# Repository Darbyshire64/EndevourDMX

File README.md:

# EndevourDMX
This is a custom DMX Tranciver Platform Designed for both reciving and controling DMX. Using an ESP32-C3 With Onboard WIFI

>[!Warning]
> Use This PCB at your own Risk. I cannot take liability if it breake's and or causes damage to equipment. This has not been tested and there is no garrentee of upholding to any level of quality/functionality.

https://github.com/user-attachments/assets/77d9e712-4af0-4d90-8f60-33b776832eaa

## Curently Availible Firmware Modes
  - Cable Tester
  - Light Controler

## Goals
  - Control One DMX Universe
  - Recive DMX and make signal qaulity Reports.
  - WIFI Based Control.
  - Display Status and Other INFO With Inbuilt OLED

## How It Works

It allows for DMX Passthrough so if something where to hapen to the MCU the DMX signal Could still passthrough pasiveley without power. The A,B Data lines are protected by a TVS Diode and 100 ohm resistors this cleans up any interfearence in the transmision. this is then sent the the MAX845E Chip to convert the data into easy to recive serieal data for the ESP. As the DMX lighting protocol uses RS845 Serieal the MAX845E is neccesary to control TX/RX the signal.

# Photos
## PCB

## Case

# BOM

I know this BOM is Expensive But its cheaper than the equivlent device i was trying to redesign but better, Called MyDMX 3.0 witch is 401.74 USD

<a href="https://www.djkit.com/products/american-dj-mydmx-30?variant=51192390254925&country=GB&currency=GBP&utm_medium=product_sync&utm_source=google&utm_content=sag_organic&utm_campaign=sag_organic"> LINK </a>

| QTY | Item                    | Price   | Link        |
|-----|-------------------------|---------|-------------|
|     | PCB Total               | $14.59  |             |
|     | Component Total         | $38.81 |             |
|     | Case Total              | $4.50   |             |
|     | Misc Total              | $13.36   |             |
|     | Total                   | $71.27   |             |

## PCB 

| QTY | Item                    | Price   | Link        |
|-----|-------------------------|---------|-------------|
|  5  | Custom Blue LF HASL PCB | $9.40  |             |
|     | Shipping (GSDL)         | $5.19   |             |
|     | Total                   | $14.59  |             |

## Components

I have chosen Digikey because it has all of my components vs LCSC who has a few of my components in stock as of making the BOM. it would be more cost effective  to buy all the components in one go rather than by two lots of shipping and handeling fees. and A OLEDs components are cheaper via Ali Express.

### Digikey
| QTY | Item                    | Price  | Link        |
|-----|-------------------------|---------|-------------|
|  2  | 1.5KE15CA        | $0.34 | <a href="https://www.digikey.co.uk/en/products/detail/stmicroelectronics/1-5KE15CA/1037261">LINK</a> |
|  1  | 1N4007           | $0.10 | <a href="https://www.digikey.co.uk/en/products/detail/diotec-semiconductor/1N4007/18833652">LINK</a> |
|  1  | MFR-25FBF52-1K8  | $0.10 | <a href="https://www.digikey.co.uk/en/products/detail/yageo/MFR-25FBF52-1K8/9138063">LINK</a> |
|  1  | CFR-12JB-52-3K3  | $0.10 | <a href="https://www.digikey.co.uk/en/products/detail/yageo/CFR-12JB-52-3K3/3989">LINK</a> |
|  2  | MFR-25FBF52-100R | $0.10 | <a href="https://www.digikey.co.uk/en/products/detail/yageo/MFR-25FBF52-100R/12795">LINK</a> |
|  1  | MFR-25FBF52-120R | $0.10 | <a href="https://www.digikey.co.uk/en/products/detail/yageo/MFR-25FTE52-120R/9139747">LINK</a> |
|  1  | 2N3904           | $0.14 | <a href="https://www.digikey.co.uk/en/products/detail/diotec-semiconductor/2N3904/13164701">LINK</a> |
|  3  | WS281B           | $0.68 | <a href="https://www.digikey.co.uk/en/products/detail/sparkfun-electronics/16347/11630204">LINK</a> |
|  1  | MAX485ECSA+      | $5.88 | <a href="https://www.digikey.co.uk/en/products/detail/analog-devices-inc-maxim-integrated/MAX485ECSA/1495336">LINK</a> |
|  1  | IO-XLR3-F-EH     | $2.63 | <a href="https://www.digikey.co.uk/en/products/detail/io-audio-technologies/IO-XLR3-F-EH/9931888">LINK</a> |
|  1  | IO-XLR3-M-EH     | $2.55 | <a href="https://www.digikey.co.uk/en/products/detail/io-audio-technologies/IO-XLR3-M-EH/9931887">LINK</a> |
|  1  | XIAO ESP-32-C3   | $4.99 | <a href="https://www.digikey.co.uk/en/products/detail/seeed-technology-co-ltd/113991054/16652880">LINK</a> |
|  1  | 2.4Ghz Atenna    | $2.20 | <a href="https://www.digikey.co.uk/en/products/detail/seeed-technology-co-ltd/103990623/18724506">LINK</a> |
|  1  | Headers          | $0.24 | <a href="https://www.digikey.co.uk/en/products/detail/seeed-technology-co-ltd/102010490/19176770">LINK</a> |
|     | Shiping          | $6.88 | |
|     | Total Excl Shiping| $21.95 | |
|     | Total Incl Shiping| $29.84 | |

### AliExpress

| QTY | Item                    | Price  | Link        |
|-----|-------------------------|---------|-------------|
|  1  | OLED DISPLAY        | $5.35 | <a href="https://www.aliexpress.com/item/1005008988479159.html?spm=a2g0o.detail.0.0.3f8dP1SHP1SHRr&mp=1&pdp_npi=5%40dis%21USD%21USD%205.35%21USD%202.62%21%21USD%202.62%21%21%21%40211b628117536181461324433e3141%2112000047475624684%21ct%21UK%21-1%21%211%210">LINK</a> |
| | Total Excl Shiping | $5.35 |
| | Toatl Incl Shiping | $8.34 |

## Case

Printed With Printing Legion. Estmiated Shiping Cost Based on prevoious printing legion experiance.

| QTY | Item                    | Price   | Link        |
|-----|-------------------------|---------|-------------|
|  1  | Case                    | $4.50   |             |

## Tool's & Misc

| QTY | Item                    | Price   | Link        |
|-----|-------------------------|---------|-------------|
|  1  | 10g Flux                | $3.32   | <a href="https://www.aliexpress.com/item/1005008562727265.html?spm=a2g0o.detail.0.0.1891tDgOtDgOiD&mp=1&pdp_npi=5%40dis%21USD%21USD%203.32%21USD%200.99%21%21USD%200.99%21%21%21%40211b628117536181317473986e3141%2112000045736601174%21ct%21UK%21-1%21%211%210"> LINK </a> |
|  1  | 50g Solder              | $10.89  | <a href="https://www.aliexpress.com/item/1005007330449968.html?spm=a2g0o.detail.0.0.d802qv9rqv9rOF&mp=1&pdp_npi=5%40dis%21USD%21USD%2010.89%21USD%205.44%21%21USD%205.44%21%21%21%40211b628117536180518621644e3141%2112000040294388218%21ct%21UK%21-1%21%211%210"> LINK </a> |
|  1  | M3 Heatset Inserts      | $2.03   | <a href="https://www.aliexpress.com/item/1005003582355741.html?spm=a2g0o.detail.0.0.330ciNNZiNNZhx&mp=1&pdp_npi=5%40dis%21USD%21USD%202.03%21USD%202.03%21%21USD%202.03%21%21%21%40211b628117536180843722706e3141%2112000026370649756%21ct%21UK%21-1%21%211%210"> LINK </a>  |
|  1  | M3x14mm Screws          | $2.94   | <a href="https://www.aliexpress.com/item/32867841097.html?spm=a2g0o.cart.0.0.5a5b38dafIVPIo&mp=1&pdp_npi=5%40dis%21USD%21USD%202.94%21USD%202.65%21%21USD%202.65%21%21%21%402103892f17536178038338142eac37%2165441947149%21ct%21UK%21-1%21%211%210"> LINK </a> |
| | Total No Discount & Shiping | $19.81 |
| | Total Incl Discounts & Shiping | $13.36|

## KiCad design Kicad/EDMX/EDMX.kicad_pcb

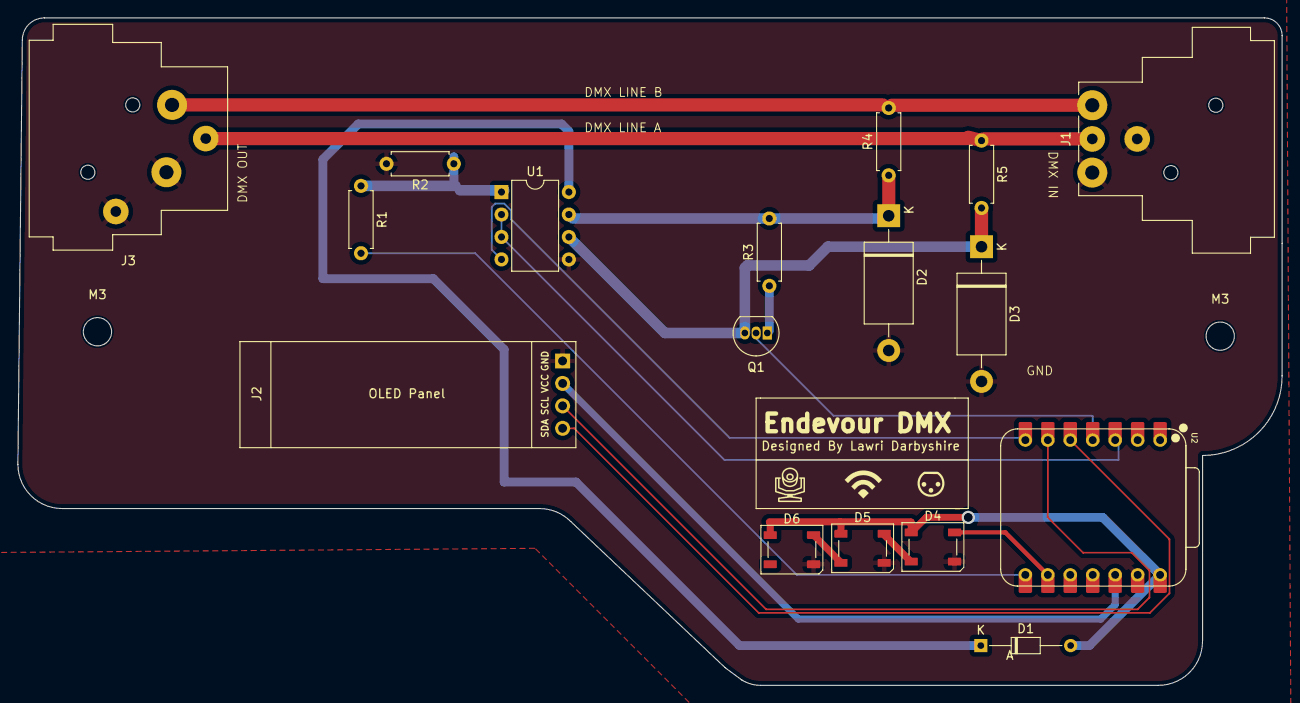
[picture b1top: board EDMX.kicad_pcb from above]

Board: 2 copper layers, 143.0 x 75.5 mm, 19 parts (0 on the bottom side), 18 nets.

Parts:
D1: D; D_DO-34_SOD68_P10.16mm_Horizontal
D2, D3: 1.5KExxCA; D_DO-201AE_P15.24mm_Horizontal
D4: DMX Status; LED_WS2812B_PLCC4_5.0x5.0mm_P3.2mm
D5: WiFi Status; LED_WS2812B_PLCC4_5.0x5.0mm_P3.2mm
D6: Light Control; LED_WS2812B_PLCC4_5.0x5.0mm_P3.2mm
J1: XLR3 IN; Jack_XLR_Neutrik_NC3MAAH_Horizontal
J2: Conn_01x04; SSD1306-0.91-OLED-4pin-128x32
J3: XLR3 OUT; Jack_XLR_Neutrik_NC3FAH2_Horizontal
M3, M3#2: MountingHole_3.2mm_M3
Q1: 2N3904; TO-92_Inline
R1: 3.3kΩ; R_Axial_DIN0207_L6.3mm_D2.5mm_P7.62mm_Horizontal
R2: 1.8kΩ; R_Axial_DIN0207_L6.3mm_D2.5mm_P7.62mm_Horizontal
R3: 120Ω; R_Axial_DIN0207_L6.3mm_D2.5mm_P7.62mm_Horizontal
R4, R5: 100Ω; R_Axial_DIN0207_L6.3mm_D2.5mm_P7.62mm_Horizontal
U1: MAX485E; DIP-8_W7.62mm
U2: XIAO-ESP32-C3-DIP; XIAO-ESP32C3-DIP

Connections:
/5V: R1.1, R2.1, U1.1 (RO)
GND: D2.2 (A2), D3.2 (A2), D4.3 (VSS), D5.3 (VSS), D6.3 (VSS), J1.1, J1.G, J2.1, J3.1, J3.G, R2.2, U1.5 (GND), U2.13 (GND)
unnamed: D2.1 (A1), R3.2, R4.2
unnamed: D3.1 (A1), Q1.3 (C), R5.2, U1.6 (A)
unnamed: D4.2 (DOUT), D5.4 (DIN)
unnamed: D5.2 (DOUT), D6.4 (DIN)
unnamed: J1.2, J3.2, R4.1
unnamed: J1.3, J3.3, R5.1
unnamed: Q1.1 (E), R3.1
RX: R1.2, U2.8 (GPIO20/D7/RX)
SCL: J2.3, U2.6 (GPIO7/D5/SCL)
SDA: J2.4, U2.5 (GPIO6/D4/SDA)
STATUS LIGHTS: D4.4 (DIN), U2.9 (GPIO8/D8/SCK)
TERM CONTROL: Q1.2 (B), U2.4 (GPIO5/A3/D3)
TX: U1.4 (DI), U2.7 (GPIO21/D6/TX)
TX/RX Control: U1.2 (~RE), U1.3 (DE), U2.3 (GPIO4/A2/D2)
VBUS: D1.1 (K), D1.2 (A), D4.1 (VDD), D5.1 (VDD), D6.1 (VDD), U1.8 (VCC), U2.14 (VBUS)
VCC: J2.2, U2.12 (VCC_3V3)

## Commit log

2025-07-15 Added some images
2025-07-16 Added KiCAD Project
2025-07-20 nano
2025-07-21 Updated Journal and moved the files about
2025-07-21 Did FIRMWARE
2025-07-21 Did some more FIRMWARE
2025-07-26 Added New Firmware
2025-07-27 Added New Fully Assembled PCB Model
2025-07-27 Oganised Journal.MD
2025-07-27 Added Video
2025-07-27 Made Render
2025-07-27 Renamed Files
